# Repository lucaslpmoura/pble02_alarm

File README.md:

# PBLE02 - Gerenciamento de alarme

Este projeto foi feito por [Lucas Moura](https://github.com/lucaslpmoura), [Lucas Romualdo](https://github.com/ROMUALDO-TXT) e Pedro Coelho para a disciplina PBLE02 - *Board Bring-up e Validação de Projetos*, na Universidade de Federal de Itajubá, em 2023/1.

O projeto consiste em um mockup de sistema de validação de alarmes, utilizando o microprocessador PIC18F4550 como base. 

## Dependências 
- [Kicad](https://www.kicad.org)
- [xc8](https://www.microchip.com/en-us/tools-resources/develop/mplab-xc-compilers)

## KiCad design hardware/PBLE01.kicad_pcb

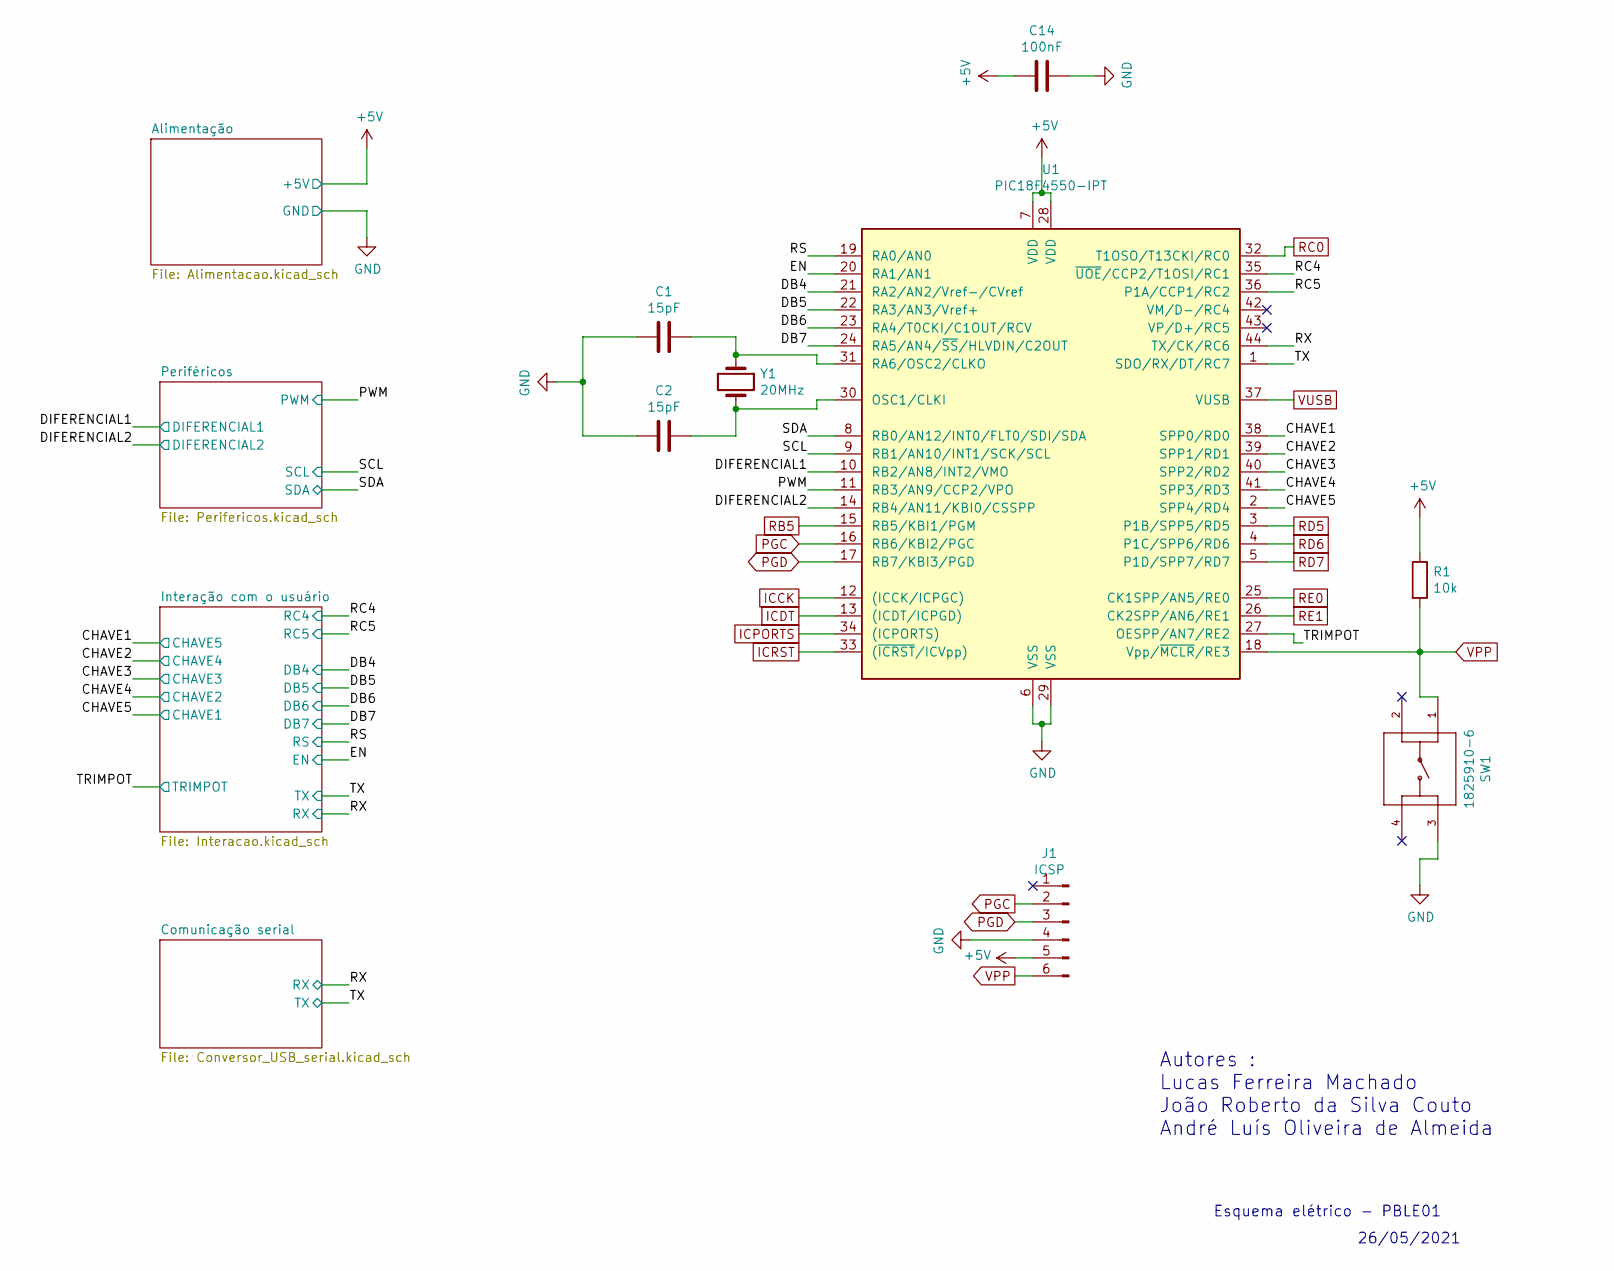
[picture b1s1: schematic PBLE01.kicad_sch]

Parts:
C1, C2: 15pF; C_0805_2012Metric_Pad1.18x1.45mm_HandSolder
C14: 100nF; C_0805_2012Metric_Pad1.18x1.45mm_HandSolder
J1: ICSP; PinHeader_1x06_P2.54mm_Vertical
R1: 10k; R_0805_2012Metric_Pad1.20x1.40mm_HandSolder
SW1: 1825910-6; SW_1825910-6-4
U1: PIC18F4550-IPT; TQFP-44_10x10mm_P0.8mm
Y1: 20MHz; Crystal_HC49-4H_Vertical

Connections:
+5V: C14.1, J1.5, R1.1, U1.7 (VDD), U1.28 (VDD); also elsewhere on the board
/CHAVE1: U1.38 (SPP0/RD0); also elsewhere on the board
/CHAVE2: U1.39 (SPP1/RD1); also elsewhere on the board
/CHAVE3: U1.40 (SPP2/RD2); also elsewhere on the board
/CHAVE4: U1.41 (SPP3/RD3); also elsewhere on the board
/CHAVE5: U1.2 (SPP4/RD4); also elsewhere on the board
/DB4: U1.21 (RA2/AN2/Vref-/CVref); also elsewhere on the board
/DB5: U1.22 (RA3/AN3/Vref+); also elsewhere on the board
/DB6: U1.23 (RA4/T0CKI/C1OUT/RCV); also elsewhere on the board
/DB7: U1.24 (RA5/AN4/~SS/HLVDIN/C2OUT); also elsewhere on the board
/DIFERENCIAL1: U1.10 (RB2/AN8/INT2/VMO); also elsewhere on the board
/DIFERENCIAL2: U1.14 (RB4/AN11/KBI0/CSSPP); also elsewhere on the board
/EN: U1.20 (RA1/AN1); also elsewhere on the board
/PWM: U1.11 (RB3/AN9/CCP2/VPO); also elsewhere on the board
/RC4: U1.35 (~UOE/CCP2/T1OSI/RC1); also elsewhere on the board
/RC5: U1.36 (P1A/CCP1/RC2); also elsewhere on the board
/RS: U1.19 (RA0/AN0); also elsewhere on the board
/RX: U1.44 (TX/CK/RC6); also elsewhere on the board
/SCL: U1.9 (RB1/AN10/INT1/SCK/SCL); also elsewhere on the board
/SDA: U1.8 (RB0/AN12/INT0/FLT0/SDI/SDA); also elsewhere on the board
/TRIMPOT: U1.27 (OESPP/AN7/RE2); also elsewhere on the board
/TX: U1.1 (SDO/RX/DT/RC7); also elsewhere on the board
GND: C1.1, C2.1, C14.2, J1.4, SW1.3, U1.6 (VSS), U1.29 (VSS); also elsewhere on the board
ICCK: U1.12 ((ICCK/ICPGC)); also elsewhere on the board
ICDT: U1.13 ((ICDT/ICPGD)); also elsewhere on the board
ICPORTS: U1.34 ((ICPORTS)); also elsewhere on the board
ICRST: U1.33 ((~ICRST/ICVpp)); also elsewhere on the board
unnamed: C1.2, U1.31 (RA6/OSC2/CLKO), Y1.1
unnamed: C2.2, U1.30 (OSC1/CLKI), Y1.2
PGC: J1.2, U1.16 (RB6/KBI2/PGC)
PGD: J1.3, U1.17 (RB7/KBI3/PGD)
RB5: U1.15 (RB5/KBI1/PGM); also elsewhere on the board
RC0: U1.32 (T1OSO/T13CKI/RC0); also elsewhere on the board
RD5: U1.3 (P1B/SPP5/RD5); also elsewhere on the board
RD6: U1.4 (P1C/SPP6/RD6); also elsewhere on the board
RD7: U1.5 (P1D/SPP7/RD7); also elsewhere on the board
RE0: U1.25 (CK1SPP/AN5/RE0); also elsewhere on the board
RE1: U1.26 (CK2SPP/AN6/RE1); also elsewhere on the board
VPP: J1.6, R1.2, SW1.1, U1.18 (Vpp/~MCLR/RE3)
VUSB: U1.37 (VUSB); also elsewhere on the board

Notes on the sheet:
26/05/2021
Autores : Lucas Ferreira Machado João Roberto da Silva Couto André Luís Oliveira de Almeida
Esquema elétrico - PBLE01

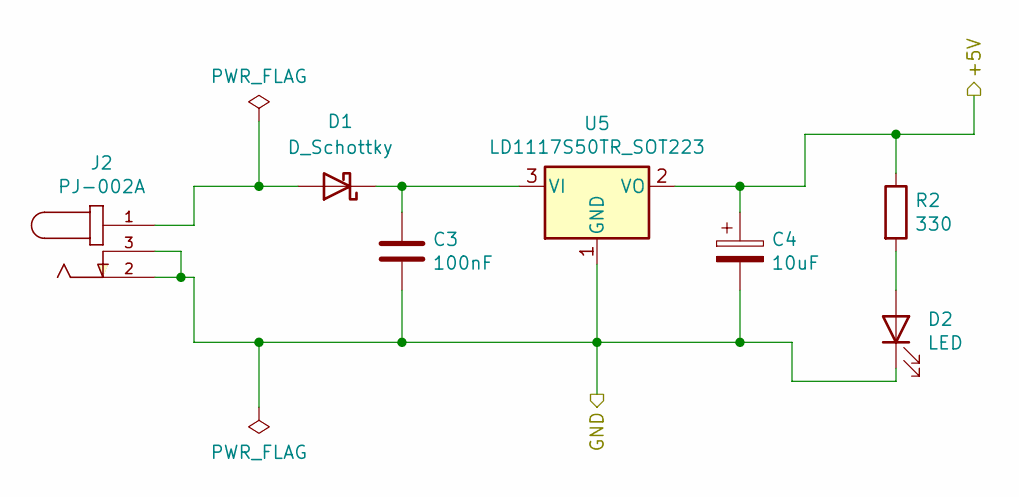
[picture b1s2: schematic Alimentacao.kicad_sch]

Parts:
C3: 100nF; C_0805_2012Metric_Pad1.18x1.45mm_HandSolder
C4: 10uF; CAPPM3216X180N
D1: D_Schottky; D_0603_1608Metric
D2: LED; LTST-C150GKT
J2: PJ-002A; CUI_PJ-002A
R2: 330; R_0805_2012Metric_Pad1.20x1.40mm_HandSolder
U5: LD1117S50TR_SOT223; TO-252-3_TabPin2

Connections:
+5V: C4.1, R2.1, U5.2 (VO); also elsewhere on the board
GND: C3.2, C4.2, D2.1 (K), J2.2, J2.3, U5.1 (GND); also elsewhere on the board
unnamed: C3.1, D1.1 (K), U5.3 (VI)
unnamed: D1.2 (A), J2.1
unnamed: D2.2 (A), R2.2

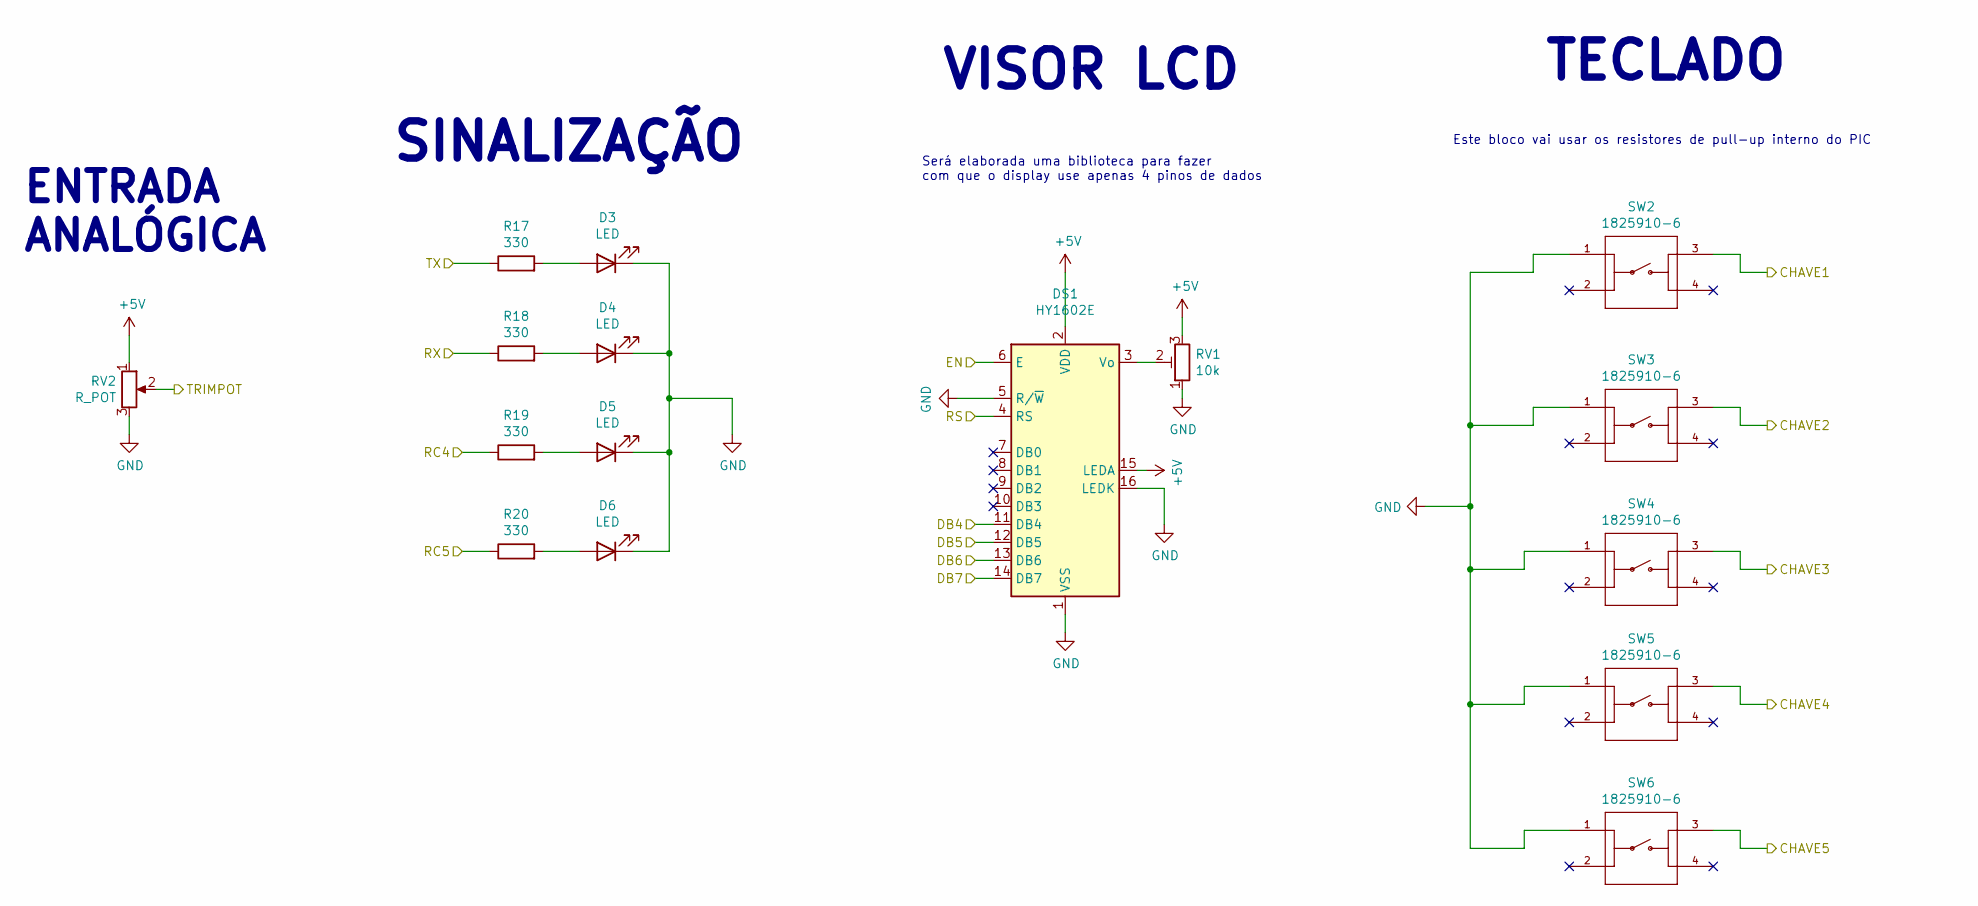
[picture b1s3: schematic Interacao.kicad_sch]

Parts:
D3, D4, D5, D6: LED; LTST-C150GKT
DS1: HY1602E
R17, R18, R19, R20: 330; R_0805_2012Metric_Pad1.20x1.40mm_HandSolder
RV1: 10k; Potentiometer_Bourns_3296W_Vertical
RV2: R_POT; P160KN0QC15B100K
SW2, SW3, SW4, SW5, SW6: 1825910-6; SW_1825910-6-4

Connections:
+5V: DS1.2 (VDD), DS1.15 (LEDA), RV1.3, RV2.1; also elsewhere on the board
/CHAVE1: SW6.3; also elsewhere on the board
/CHAVE2: SW5.3; also elsewhere on the board
/CHAVE3: SW4.3; also elsewhere on the board
/CHAVE4: SW3.3; also elsewhere on the board
/CHAVE5: SW2.3; also elsewhere on the board
/DB4: DS1.11 (DB4); also elsewhere on the board
/DB5: DS1.12 (DB5); also elsewhere on the board
/DB6: DS1.13 (DB6); also elsewhere on the board
/DB7: DS1.14 (DB7); also elsewhere on the board
/EN: DS1.6 (E); also elsewhere on the board
/RC4: R19.1; also elsewhere on the board
/RC5: R20.1; also elsewhere on the board
/RS: DS1.4 (RS); also elsewhere on the board
/RX: R18.1; also elsewhere on the board
/TRIMPOT: RV2.2; also elsewhere on the board
/TX: R17.1; also elsewhere on the board
GND: D3.1 (K), D4.1 (K), D5.1 (K), D6.1 (K), DS1.1 (VSS), DS1.5 (R/~W), DS1.16 (LEDK), RV1.1, RV2.3, SW2.1, SW3.1, SW4.1, SW5.1, SW6.1; also elsewhere on the board
unnamed: D3.2 (A), R17.2
unnamed: D4.2 (A), R18.2
unnamed: D5.2 (A), R19.2
unnamed: D6.2 (A), R20.2
unnamed: DS1.3 (Vo), RV1.2

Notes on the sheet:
Será elaborada uma biblioteca para fazer com que o display use apenas 4 pinos de dados
ENTRADA ANALÓGICA
TECLADO
Este bloco vai usar os resistores de pull-up interno do PIC
VISOR LCD
SINALIZAÇÃO

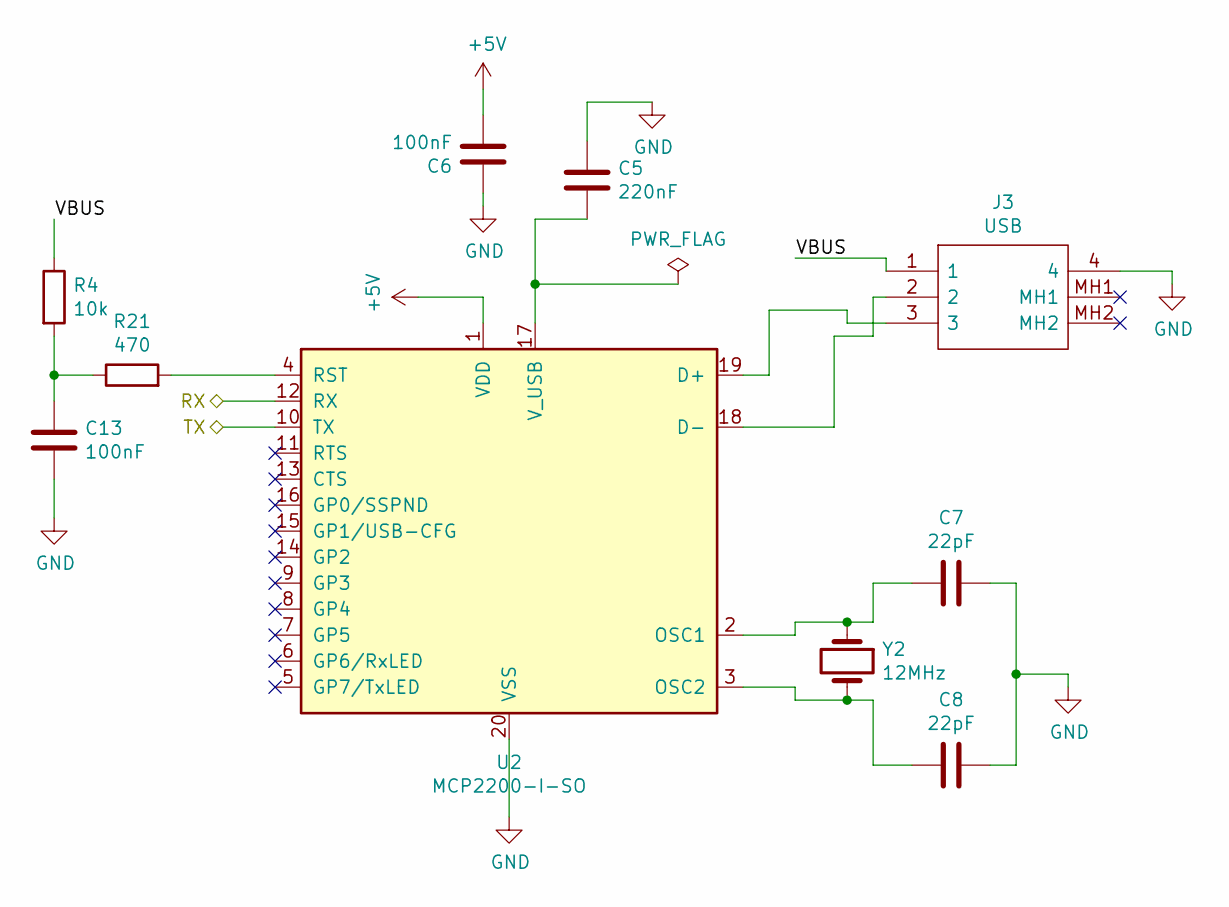
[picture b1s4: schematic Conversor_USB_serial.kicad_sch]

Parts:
C5: 220nF; C_0805_2012Metric_Pad1.18x1.45mm_HandSolder
C6, C13: 100nF; C_0805_2012Metric_Pad1.18x1.45mm_HandSolder
C7, C8: 22pF; C_0805_2012Metric_Pad1.18x1.45mm_HandSolder
J3: USB; 8974300490000000; Mouser Part Number 575-8974349
R4: 10k; R_0805_2012Metric_Pad1.20x1.40mm_HandSolder
R21: 470; R_0805_2012Metric_Pad1.20x1.40mm_HandSolder
U2: MCP2200-I-SO; SOIC-20W_7.5x12.8mm_P1.27mm
Y2: 12MHz; Crystal_HC49-4H_Vertical

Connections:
+5V: C6.2, U2.1 (VDD); also elsewhere on the board
/Comunicação serial /VBUS: J3.1, R4.1
/RX: U2.12 (RX); also elsewhere on the board
/TX: U2.10 (TX); also elsewhere on the board
GND: C5.1, C6.1, C7.1, C8.2, C13.2, J3.4, U2.20 (VSS); also elsewhere on the board
unnamed: C5.2, U2.17 (V_USB)
unnamed: C7.2, U2.2 (OSC1), Y2.1
unnamed: C8.1, U2.3 (OSC2), Y2.2
unnamed: C13.1, R4.2, R21.1
unnamed: J3.2, U2.18 (D-)
unnamed: J3.3, U2.19 (D+)
unnamed: R21.2, U2.4 (RST)

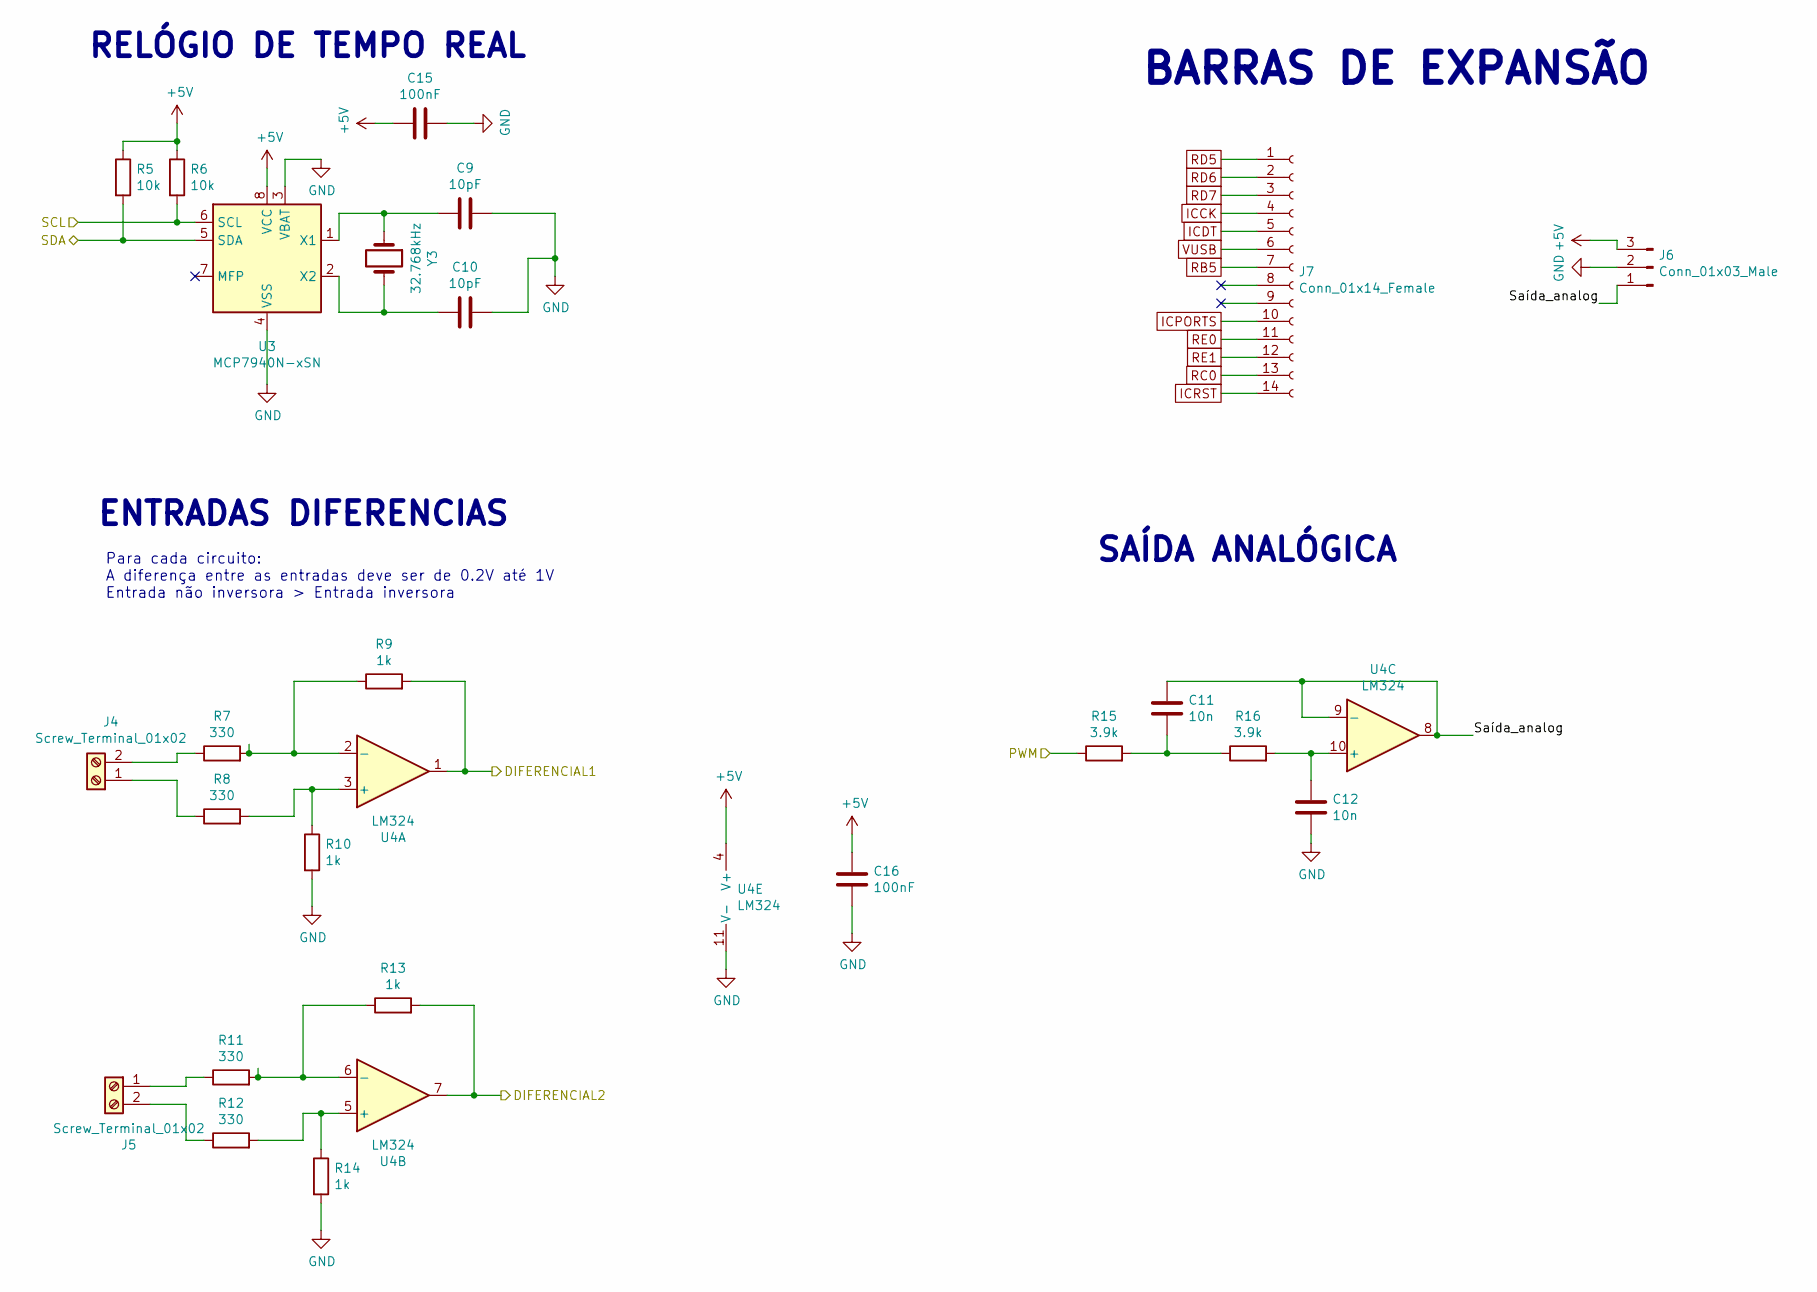
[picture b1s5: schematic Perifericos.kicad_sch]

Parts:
C9, C10: 10pF; C_0805_2012Metric_Pad1.18x1.45mm_HandSolder
C11, C12: 10n; C_0805_2012Metric_Pad1.18x1.45mm_HandSolder
C15, C16: 100nF; C_0805_2012Metric_Pad1.18x1.45mm_HandSolder
J4, J5: Screw_Terminal_01x02; TerminalBlock_MetzConnect_Type011_RT05502HBWC_1x02_P5.00mm_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
J6: Conn_01x03_Male; PinHeader_1x03_P2.54mm_Vertical
J7: Conn_01x14_Female; PinSocket_1x14_P2.54mm_Vertical
R5, R6: 10k; R_0805_2012Metric_Pad1.20x1.40mm_HandSolder
R7, R8, R11, R12: 330; R_0805_2012Metric_Pad1.20x1.40mm_HandSolder
R9, R10, R13, R14: 1k; R_0805_2012Metric_Pad1.20x1.40mm_HandSolder
R15, R16: 3.9k; R_0805_2012Metric_Pad1.20x1.40mm_HandSolder
U3: MCP7940N-xSN; SOIC127P600X175-8N
U4: LM324; SOIC127P600X175-14N
Y3: 32.768kHz; XTAL_AB38T-32.768KHZ

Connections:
+5V: C15.1, C16.1, J6.3, R5.1, R6.1, U3.8 (VCC), U4.4 (V+); also elsewhere on the board
/DIFERENCIAL1: R9.2, U4.1; also elsewhere on the board
/DIFERENCIAL2: R13.2, U4.7; also elsewhere on the board
/PWM: R15.1; also elsewhere on the board
/Periféricos/Saída_analog: C11.1, J6.1, U4.8, U4.9 (-)
/SCL: R6.2, U3.6 (SCL); also elsewhere on the board
/SDA: R5.2, U3.5 (SDA); also elsewhere on the board
GND: C9.1, C10.2, C12.2, C15.2, C16.2, J6.2, R10.2, R14.2, U3.3 (VBAT), U3.4 (VSS), U4.11 (V-); also elsewhere on the board
ICCK: J7.4; also elsewhere on the board
ICDT: J7.5; also elsewhere on the board
ICPORTS: J7.10; also elsewhere on the board
ICRST: J7.14; also elsewhere on the board
unnamed: C9.2, U3.1 (X1), Y3.1
unnamed: C10.1, U3.2 (X2), Y3.2
unnamed: C11.2, R15.2, R16.1
unnamed: C12.1, R16.2, U4.10 (+)
unnamed: J4.1, R8.1
unnamed: J4.2, R7.1
unnamed: J5.1, R11.1
unnamed: J5.2, R12.1
unnamed: R7.2, R9.1, U4.2 (-)
unnamed: R8.2, R10.1, U4.3 (+)
unnamed: R11.2, R13.1, U4.6 (-)
unnamed: R12.2, R14.1, U4.5 (+)
RB5: J7.7; also elsewhere on the board
RC0: J7.13; also elsewhere on the board
RD5: J7.1; also elsewhere on the board
RD6: J7.2; also elsewhere on the board
RD7: J7.3; also elsewhere on the board
RE0: J7.11; also elsewhere on the board
RE1: J7.12; also elsewhere on the board
VUSB: J7.6; also elsewhere on the board

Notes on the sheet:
ENTRADAS DIFERENCIAS
BARRAS DE EXPANSÃO
RELÓGIO DE TEMPO REAL
SAÍDA ANALÓGICA
Para cada circuito: A diferença entre as entradas deve ser de 0.2V até 1V Entrada não inversora > Entrada inversora

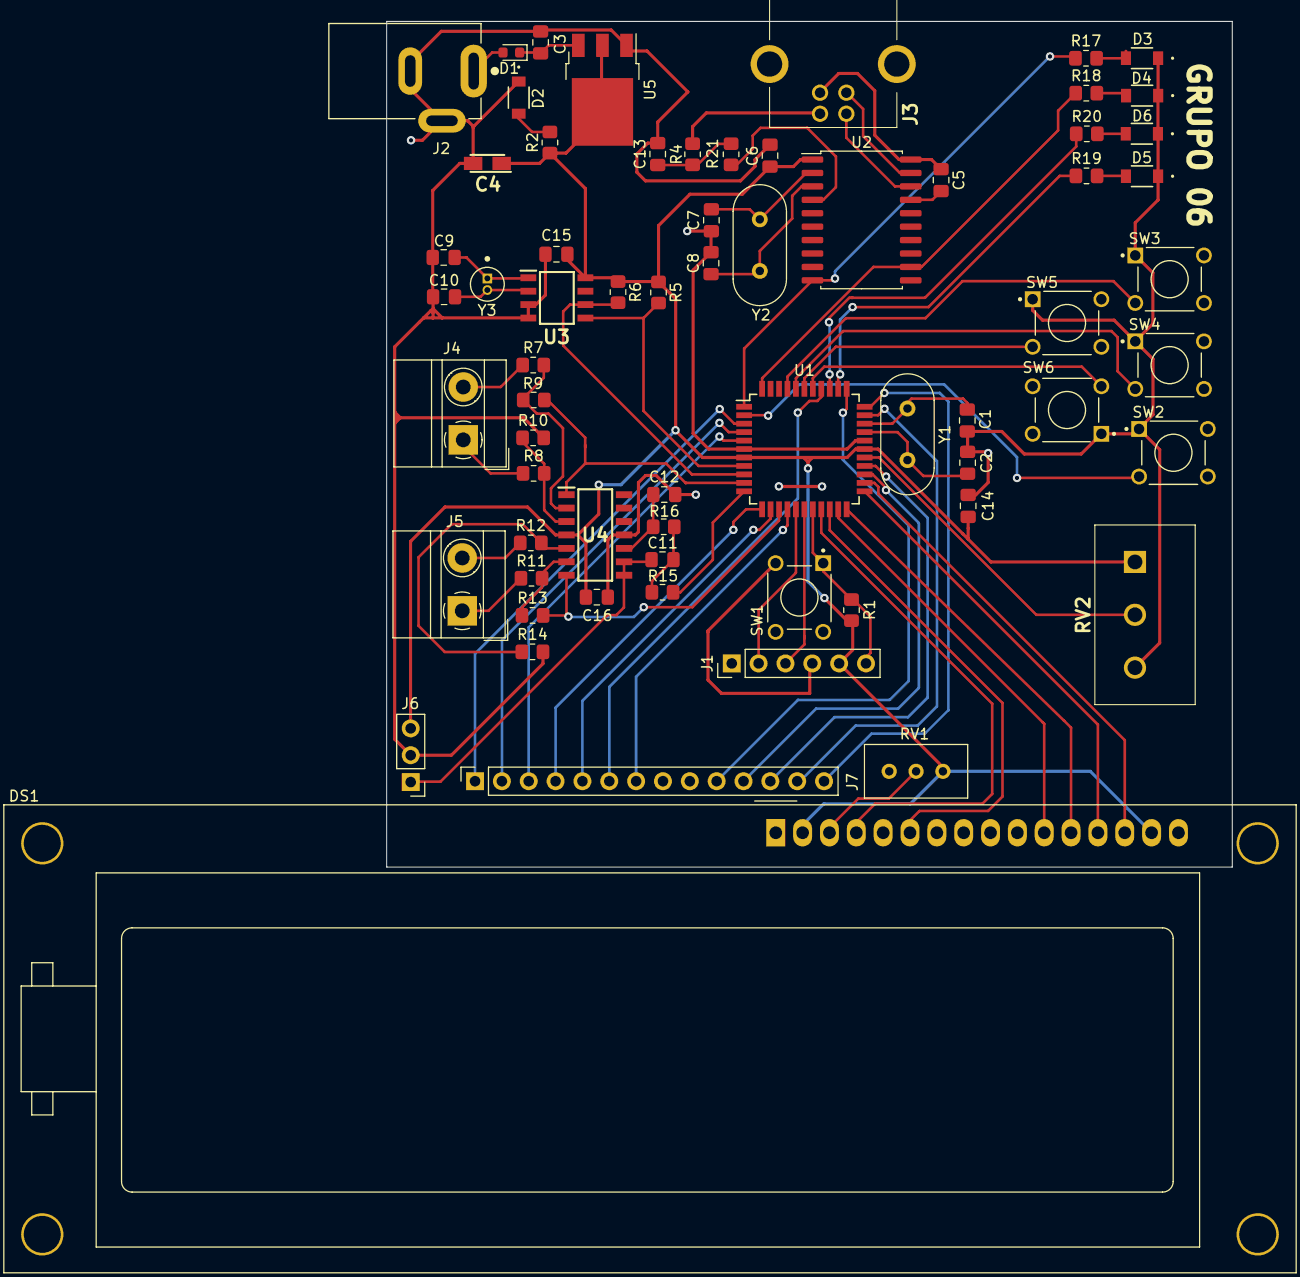
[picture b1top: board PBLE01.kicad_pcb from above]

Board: 2 copper layers, 80.0 x 80.0 mm, 66 parts (0 on the bottom side), 69 nets.

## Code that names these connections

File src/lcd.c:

// -----------------------------------------------------------------------
//   Copyright (C) Rodrigo Almeida 2010
// -----------------------------------------------------------------------
//   Arquivo: lcd.c
//            Biblioteca de manipula??o do LCD
//   Autor:   Rodrigo Maximiano Antunes de Almeida
//            rodrigomax at unifei.edu.br
//   Licen?a: GNU GPL 2
// -----------------------------------------------------------------------
//   This program is free software; you can redistribute it and/or modify
//   it under the terms of the GNU General Public License as published by
//   the Free Software Foundation; version 2 of the License.
//
//   This program is distributed in the hope that it will be useful,
//   but WITHOUT ANY WARRANTY; without even the implied warranty of
//   MERCHANTABILITY or FITNESS FOR A PARTICULAR PURPOSE.  See the
//   GNU General Public License for more details.
// -----------------------------------------------------------------------


#include "lcd.h"
#include "bits.h"
#include "serial.h"
#include <pic18f4550.h>
//portd
#define RS 0
#define EN 1
//portB
#define DB4 2 
#define DB5 3
#define DB6 4
#define DB7 5

void Delay40us(void) {
    unsigned char j;
    for (j = 0; j < 68; j++);
}

void Delay2ms(void) {
    unsigned char j, k;
    for (j = 0; j < 20; j++)
        for (k = 0; k < 178; k++);
}

void pulseEnable() {
    PORTAbits.RA1 = 1;
    PORTAbits.RA1 = 0;
}

void lcdCommand4bits(unsigned char cmd, unsigned char data) {
   
    if(data){
        PORTAbits.RA0 = 1;
    }else{
        PORTAbits.RA0 = 0;
    }
    
    
    if (bitTst(cmd, 7)) {
        PORTAbits.RA5 = 1;
    } else {
        PORTAbits.RA5 = 0;
    }


    if (bitTst(cmd, 6)) {
        PORTAbits.RA4 = 1;
    } else {
        PORTAbits.RA4 = 0;
    }


    if (bitTst(cmd, 5)) {
        PORTAbits.RA3 = 1;
    } else {
        PORTAbits.RA3 = 0;
    }


    if (bitTst(cmd, 4)) {
        PORTAbits.RA2 = 1;
    } else {
        PORTAbits.RA2 = 0;
    }

    pulseEnable();
}

void lcdCommand(unsigned char cmd) {
    lcdCommand4bits(cmd, 0);
    lcdCommand4bits(cmd << 4, 0);


    if ((cmd == 0x02) || (cmd == 0x01)) {
        Delay2ms();
    } else {
        Delay40us();
    }
}

void lcdData(unsigned char valor) {
    lcdCommand4bits(valor, 1);
    lcdCommand4bits(valor << 4, 1);    
    Delay40us();

}

void lcdInt(int val) {
    //lcdData((val / 10000) % 10 + 48);
    //lcdData((val / 1000) % 10 + 48);
    lcdData((val / 100) % 10 + 48);
    lcdData((val / 10) % 10 + 48);
    lcdData((val / 1) % 10 + 48);
}

void lcdString(char msg[]) {
    int i = 0;
	while (msg[i] != 0) {
		lcdData(msg[i]);
		i++;
	}
}

void lcdPosition(int line, int col) {
	if (line == 0) {
		lcdCommand(0x80 + (col % 16));
	}
	if (line == 1) {
		lcdCommand(0xC0 + (col % 16));
	}
}

void lcdInit(void) {
    unsigned char i;
    // configura??es de dire??o dos terminais
    TRISA = 0x00;   
    bitClr(SPPCFG, 5);
    ADCON1 = 0b00001111; //apenas

    
    PORTAbits.RA0 = 0;
    // garante inicializa??o do LCD (+-15ms)
    for (i = 0; i < 7; i++)
        Delay2ms();

    //precisa enviar 4x pra garantir 8 bits
    lcdCommand4bits(0x30, 0); //8bits, 2 linhas, 5x8
    Delay2ms();

    lcdCommand4bits(0x30, 0); //8bits, 2 linhas, 5x8
    Delay2ms();

    lcdCommand4bits(0x30, 0); //8bits, 2 linhas, 5x8
    Delay2ms();

    lcdCommand4bits(0x20, 0); //4bits
    Delay2ms();

    lcdCommand(0x28); //4bits
    lcdCommand(0x06); //modo incremental
    lcdCommand(0x0F); //display e cursor on, com blink
    lcdCommand(0x01); //limpar display
}

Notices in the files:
parts and their libraries:
Copyright 2016 Accelerated Designs. All rights reserved.
